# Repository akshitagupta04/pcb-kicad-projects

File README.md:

# PCB-based Hardware Design — KiCad Projects

<p align="justify">
Hands-on experience in 2-layer PCB Design, including schematic, custom symbol & footprint, PCB layout, DRC, and Gerber files, in KiCad 9.0. Developing projects in 2-layer PCB-based hardware Design in KiCad 9.0. 
</p>

This repository is organized as follows: 

- **Learning Lab:** Basic, foundational PCB design projects.
- **Skill Development:** Intermediate or advance level projects from training or tutorial.

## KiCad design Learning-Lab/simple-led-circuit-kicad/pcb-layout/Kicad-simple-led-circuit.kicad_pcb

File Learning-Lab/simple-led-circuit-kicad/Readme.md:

# Simple LED Circuit – KiCad PCB Design 

## Overview
<p align="justify">
This project is my first complete 2-layer Printed Circuit Board (PCB) design, created entirely in KiCad 9.0. It is simple LED circuit based on a beginner tutorial. The project involved drawing a schematic, designing the board layout, and generating the manufacturing files. 
</p> 

---

## Circuit Description
This is a basic circuit showing how to connect an LED to a power source with a current-limiting resistor. The design uses through-hole components. 

- **Power Input:** 9V battery (designed with a two-pin header for a battery clip connection)
- **Current Limiting Resistor:** 470Ω
- **LED Indicator:** 2V Red LED 

---

## Tools Used
- **KiCad:** For schematic capture, PCB layout, and Gerber file generation. 

---

## Design Process
The board was designed in KiCad following these steps:
 
1. **Schematic Capture:** <p align="justify"> Drew the circuit diagram, placed the battery, resiator, and LED symbols, and connected their pins with wires. Annotated the schematic to give components unique values (resistor value = 470 (ohm), battery value = 9V, LED value = 2V RED). 
</p> 

2. **Footprint Assignment:** <p align="justify"> Assigned physical footprints from the KiCad library to each schematic symbol (e.g., a ***Resistor_THT*** footprint for the resistor, ***LED_THT*** for the LED, and a ***Connector_PinHeader_2.54mm*** for the battery connection). 
</p>

3. **Electrical Rules Check (ERC):** <p align="justify"> Checked the schematic to confirm no electrical errors were present.
</p>

4. **Bill of Materials (BOM):** <p align="justify"> Generated the BOM from the schematic, listing all components with values, footprints, and datasheet links.
</p>

5. **PCB Layout:** <p align="justify"> Opened the board editor, placed the footprints in an organized way, and drew copper tracks to connect them according to the schematic. 
</p>

6. **Board Outline:** <p align="justify"> Drew the physical edge of the board on the Edge.Cuts layer. 
</p>

7. **Design Rules Check (DRC):** <p align="justify"> Checked the layout for physical errors, like tracks placed too close, to confirm no physical errors were present. 
</p>

8. **Manufacturing Output:** <p align="justify"> Generated the Gerber and Drill files needed for fabrication, and the Footprint Position (.pos) file for automated assembly. 
</p>

---

## Repository Structure

```text
/simple-led-circuit-kicad/
 ├────── gerber-files/   # Manufacturing files (Gerber, Drill and Fabrication position)
 ├────── pcb-layout/     # Board layout file
 ├────── schematic/      # schematic and BOM files
 ├────── system-design/  # images of the board from 3D view
 └────── Readme.md       # Readme file 
``` 
---

## Learning Outcomes
<p align="justify">
By completing this project, I learned the standard KiCad workflow: schematic capture, component to footprint mapping, PCB layout, design rule checking, and generation of manufacturing output. This forms the base for all future designs. 
</p>

---

## Credits and Acknowledgement 
This design was made by following the tutorial below. The project structure and steps are based rntirely on this guide. 

- **Tutorial:** [KiCad Tutorial: Make Your First Printed Circuit Board](https://www.build-electronic-circuits.com/kicad-tutorial/)
- **Author:** Oyvind Dahl, Build Electronic Circuits

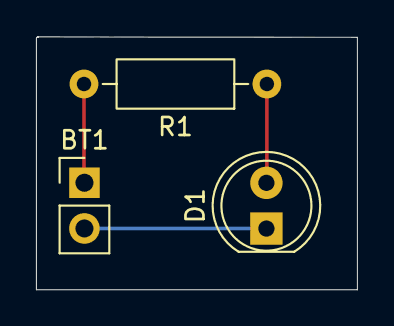
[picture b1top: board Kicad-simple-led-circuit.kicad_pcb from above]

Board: 2 copper layers, 17.8 x 14.1 mm, 3 parts (0 on the bottom side), 3 nets.

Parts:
BT1: 9V; PinHeader_1x02_P2.54mm_Vertical
D1: LED; LED_D5.0mm
R1: 470; R_Axial_DIN0207_L6.3mm_D2.5mm_P10.16mm_Horizontal

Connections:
unnamed: BT1.1 (+), R1.2
unnamed: BT1.2 (-), D1.1 (K)
unnamed: D1.2 (A), R1.1

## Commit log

2026-06-10 3d view of simple led circuit kicad pcb
2026-06-10 simple led circuit schematic
2026-06-10 simple led circuit BOM file
2026-06-10 simple led circuit pcb board layout
2026-06-10 gerber manufacturing files
2026-06-10 drilling files
2026-06-10 Fabrication Position File
